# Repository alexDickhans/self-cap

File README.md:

# Self-Cap

A small self-capacitance board from the HIRO Group. An ESP32-C6-MINI-1 reads seven electrode holes along one edge. Power comes from USB-C or a single-cell battery on a JST PH connector.

Open `self-cap.kicad_pro` in KiCad 9. The electrode-hole footprint lives in `self-cap-conn.pretty`. The silkscreen reads **HIRO Group Self-Cap PCB v1**.

## Board

Top. The ESP32-C6-MINI-1 lands on the right, and the USB-C receptacle is the pair of slots on the left. The module can and the connector shell are not drawn here; the footprints are.

Bottom. J2 is the battery connector and R2 (1 kΩ) is fitted. R3–R9 are left empty.

The board is 45.2 mm × 19.8 mm, four layers, 1.6 mm. The two inner layers are ground. Eight plated holes, 2.2 mm drill on a 5.6 mm pitch, run along the long edge. GND is the hole at the module end. Hole 7 is the hole at the USB end.

| Silkscreen | ESP32-C6 pin |
| --- | --- |
| GND | GND |
| 1 | IO23 |
| 2 | IO22 |
| 3 | IO1 |
| 4 | IO5 |
| 5 | IO4 |
| 6 | IO3 |
| 7 | IO2 |

Each numbered hole is already tied to that GPIO. R3–R9 are optional 0402 resistors on the bottom, one per hole, from the electrode to a common node. That node is driven by IO19 through R2 (1 kΩ). The value on the schematic is 1 MΩ–100 MΩ; fit whatever value you want in that range, or leave them off.

D1 is the power LED. It lights when the 3.3 V rail is up. D2 is the status LED on IO15, active high, through 330 Ω.

JP1 and JP2 are open solder jumpers. Bridge JP1 to hold EN low. Bridge JP2 to hold IO9 (BOOT) low for the serial download mode. R1 is a 100 kΩ pull-up on EN.

## Power

USB-C or the battery can run the board. U3 (SPX3819) makes 3.3 V from that input. J2 pin 1 is battery positive and pin 2 is ground. Use a single lithium cell.

U2 (MAX40200) is an ideal diode from the battery onto the 5 V rail, so USB voltage stays off the cell. There is no charger on this board.

The USB 2.0 pair and the 5.1 kΩ CC pulldown are wired on one side of the receptacle (A6, A7, and A5). If a cable does nothing, flip the plug.

## Having the board made

The files in `production/` match this revision of the board. Upload those, not an older export.

### Bare boards

1. Upload [`production/self-cap-gerbers.zip`](production/self-cap-gerbers.zip). It contains the four copper layers, solder mask, silkscreen, paste, the board outline, and one Excellon drill file.
2. Check that the preview shows a 4-layer board about 45.2 mm × 19.8 mm, with eight large round holes and two slots at the USB end.
3. Order it with these settings. They match the stackup in the KiCad file and a normal prototype fab (JLCPCB, PCBWay, and the usual Gerber upload forms).

| Setting | Value |
| --- | --- |
| Layers | 4 |
| Thickness | 1.6 mm |
| Material | FR-4 |
| Outer copper | 1 oz |
| Inner copper | 0.5 oz |
| Min trace / space | 0.15 mm / 0.2 mm |
| Smallest drill | 0.3 mm vias. Electrode holes are 2.2 mm. |
| Holes | All plated, including the electrode holes. The USB shell uses plated slots. |
| Surface finish | ENIG when the fab is soldering the USB-C connector and the module. HASL is fine if you are hand-soldering. |
| Soldermask / silk | Green soldermask and white silk match the pictures. Any color works. |
| Impedance control | Leave it off. The inner layers are a ground plane. |

The USB shell copper is 0.18 mm from the outline. If the quote warns about copper-to-edge clearance, accept it only when the shell pads are still complete in the preview.

### Assembled boards

Assembly is two-sided, but the bottom only needs J2 and R2. You can order top-side assembly and solder those two yourself.

1. Upload [`production/bom.csv`](production/bom.csv) and [`production/positions.csv`](production/positions.csv) with the gerber zip.
2. The BOM comments are the values. The LCSC column is the part number stored on the schematic. Open each LCSC page and confirm the value before you pay.
3. Parts left off the board on purpose, and omitted from both files: R3–R9, JP1, JP2, and J1. J1 is the hole pattern, not a connector.
4. On the placement preview, confirm every part sits on its pads. Check the module, the USB-C connector, both LEDs, and the two SOT-23-5 parts (U2, U3). Check J2 and R2 on the bottom. Fix any rotation in the preview before paying. The position file uses KiCad’s coordinates and rotation, and the Y values are negative, which is what KiCad writes and what JLCPCB’s KiCad import expects.

R10 (5.1 kΩ), R12, and R13 (330 Ω) use 0402 and 0603 lands. Order the resistor listed in the BOM.

## Design files

| File | What it is |
| --- | --- |
| `self-cap.kicad_pro` | KiCad 9 project |
| `self-cap.kicad_sch` | Schematic |
| `self-cap.kicad_pcb` | Board |
| `self-cap-conn.pretty/` | Electrode-hole footprint |
| `self-cap.step` | Board model |
| `production/self-cap-gerbers.zip` | Gerbers and drill file to upload |
| `production/bom.csv` | Assembly BOM |
| `production/positions.csv` | Pick-and-place file |

If you change the board, export a new gerber zip, drill file, BOM, and position file from that revision before ordering.

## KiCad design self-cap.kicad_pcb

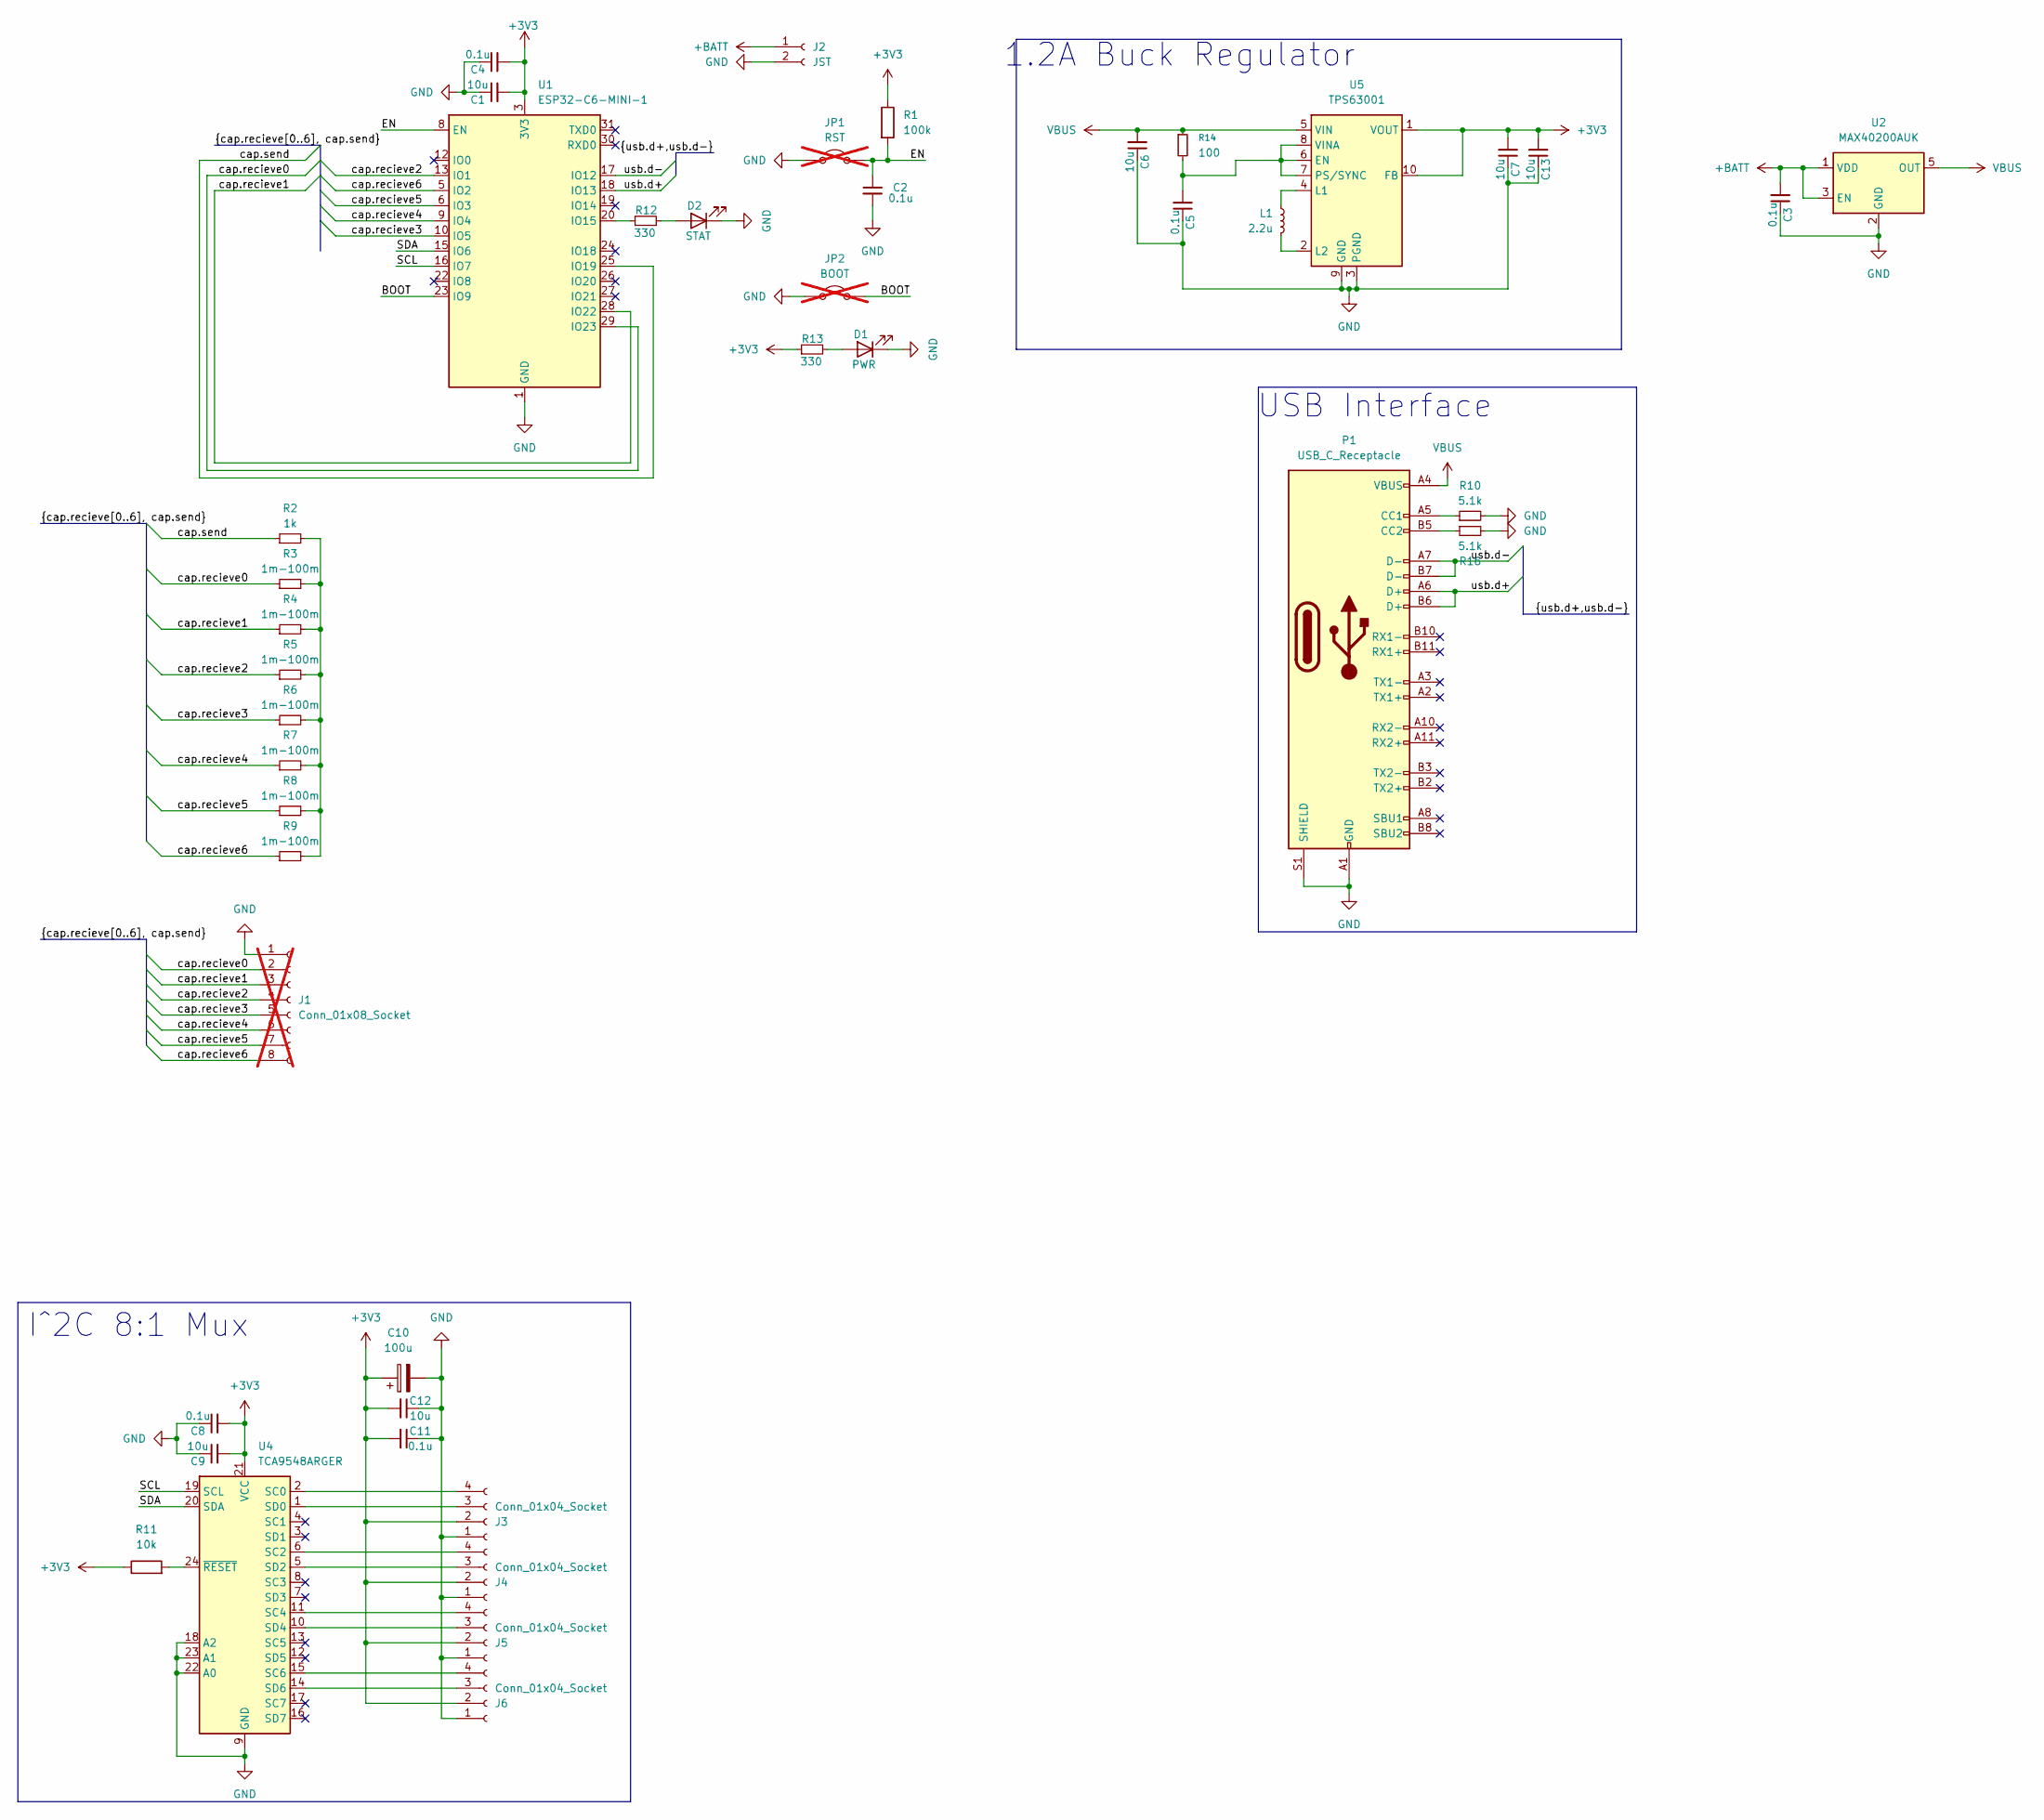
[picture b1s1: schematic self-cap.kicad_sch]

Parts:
C1, C6, C7, C9, C12, C13: 10u; C_0402_1005Metric; LCSC Part # C15525
C2, C3, C4, C5, C8, C11: 0.1u; C_0402_1005Metric; LCSC Part # C1525
C10: 100u; CP_Elec_6.3x7.7; LCSC Part # C3338
D1: PWR; LED_0603_1608Metric; LCSC Part # C2286
D2: STAT; LED_0603_1608Metric; LCSC Part # C2286
J1: Conn_01x08_Socket; self-cap-connn; not fitted
J2: JST; JST_PH_S2B-PH-SM4-TB_1x02-1MP_P2.00mm_Horizontal; LCSC Part # C295747
J3, J4, J5, J6: Conn_01x04_Socket; JST_SH_BM04B-SRSS-TB_1x04-1MP_P1.00mm_Vertical; LCSC Part # C160390
JP1: RST; SolderJumper-2_P1.3mm_Open_RoundedPad1.0x1.5mm; not fitted
JP2: BOOT; SolderJumper-2_P1.3mm_Open_RoundedPad1.0x1.5mm; not fitted
L1: 2.2u; L_Coilcraft_LPS3010; LCSC Part # C2844756
P1: USB_C_Receptacle; USB_C_Receptacle_Molex_105450-0101
R1: 100k; R_0402_1005Metric; LCSC Part # C25741
R2: 1k; R_0402_1005Metric; LCSC Part # C11702
R3, R4, R5, R6, R7, R8, R9: 1m-100m; C_0402_1005Metric; LCSC Part # C131554
R10, R16: 5.1k; C_0402_1005Metric; LCSC Part # C25905
R11: 10k; R_0402_1005Metric; LCSC Part # C25744
R12, R13: 330; C_0603_1608Metric; LCSC Part # C23138
R14: 100; R_0402_1005Metric; LCSC Part # C25076
U1: ESP32-C6-MINI-1; LCSC Part # C5736265
U2: MAX40200AUK; SOT-23-5; LCSC Part # C47118006
U4: TCA9548ARGER; Texas_RGE0024C_VQFN-24-1EP_4x4mm_P0.5mm_EP2.1x2.1mm; LCSC Part # C555456
U5: TPS63001; Texas_DRC0010J_ThermalVias; LCSC Part # C28060

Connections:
+3V3: C1.2, C4.2, C7.2, C8.2, C9.2, C10.1, C11.2, C12.2, C13.2, J3.2, J4.2, J5.2, J6.2, R1.1, R11.1, R13.1, U1.3 (3V3), U4.21 (VCC), U5.1 (VOUT), U5.10 (FB)
+BATT: C3.2, J2.1, U2.1 (VDD), U2.3 (EN)
/BOOT: JP2.2 (B), U1.23 (IO9)
/EN: C2.1, JP1.2 (B), R1.2, U1.8 (EN)
/SCL: U1.16 (IO7), U4.19 (SCL)
/SDA: U1.15 (IO6), U4.20 (SDA)
/cap.recieve0: J1.2, R3.1, U1.29 (IO23)
/cap.recieve1: J1.3, R4.1, U1.28 (IO22)
/cap.recieve2: J1.4, R5.1, U1.13 (IO1)
/cap.recieve3: J1.5, R6.1, U1.10 (IO5)
/cap.recieve4: J1.6, R7.1, U1.9 (IO4)
/cap.recieve5: J1.7, R8.1, U1.6 (IO3)
/cap.recieve6: J1.8, R9.1, U1.5 (IO2)
/cap.send: R2.1, U1.25 (IO19)
/usb.d+: P1.A6 (D+), P1.B6 (D+), U1.18 (IO13)
/usb.d-: P1.A7 (D-), P1.B7 (D-), U1.17 (IO12)
GND: C1.1, C2.2, C3.1, C4.1, C5.1, C6.1, C7.1, C8.1, C9.1, C10.2, C11.1, C12.1, C13.1, D1.1 (K), D2.1 (K), J1.1, J2.2, J3.1, J4.1, J5.1, J6.1, JP1.1 (A), JP2.1 (A), P1.A1 (GND), P1.A12 (GND), P1.B1 (GND), P1.B12 (GND), P1.S1 (SHIELD), R10.2, R16.2, U1.1 (GND), U1.2 (GND), U1.11 (GND), U1.14 (GND), U1.36 (GND), U1.37 (GND), U1.38 (GND), U1.39 (GND), U1.40 (GND), U1.41 (GND), U1.42 (GND), U1.43 (GND), U1.44 (GND), U1.45 (GND), U1.46 (GND), U1.47 (GND), U1.48 (GND), U1.49 (GND), U1.50 (GND), U1.51 (GND), U1.52 (GND), U1.53 (GND), U2.2 (GND), U4.9 (GND), U4.18 (A2), U4.22 (A0), U4.23 (A1), U5.3 (PGND), U5.9 (GND), U5.11 (PGND)
unnamed: D1.2 (A), R13.2
unnamed: D2.2 (A), R12.2
unnamed: J3.3, U4.1 (SD0)
unnamed: J3.4, U4.2 (SC0)
unnamed: J4.3, U4.5 (SD2)
unnamed: J4.4, U4.6 (SC2)
unnamed: J5.3, U4.10 (SD4)
unnamed: J5.4, U4.11 (SC4)
unnamed: J6.3, U4.14 (SD6)
unnamed: J6.4, U4.15 (SC6)
unnamed: P1.A5 (CC1), R10.1
unnamed: P1.B5 (CC2), R16.1
unnamed: R2.2, R3.2, R4.2, R5.2, R6.2, R7.2, R8.2, R9.2
unnamed: R12.1, U1.20 (IO15)
unnamed: R11.2, U4.24 (~RESET)
unnamed: C5.2, R14.2, U5.6 (EN), U5.7 (PS/SYNC), U5.8 (VINA)
unnamed: L1.1, U5.4 (L1)
unnamed: L1.2, U5.2 (L2)
VBUS: C6.2, P1.A4 (VBUS), P1.A9 (VBUS), P1.B4 (VBUS), P1.B9 (VBUS), R14.1, U2.5 (OUT), U5.5 (VIN)

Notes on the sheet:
USB Interface
1.2A Buck Regulator
I^2C 8:1 Mux

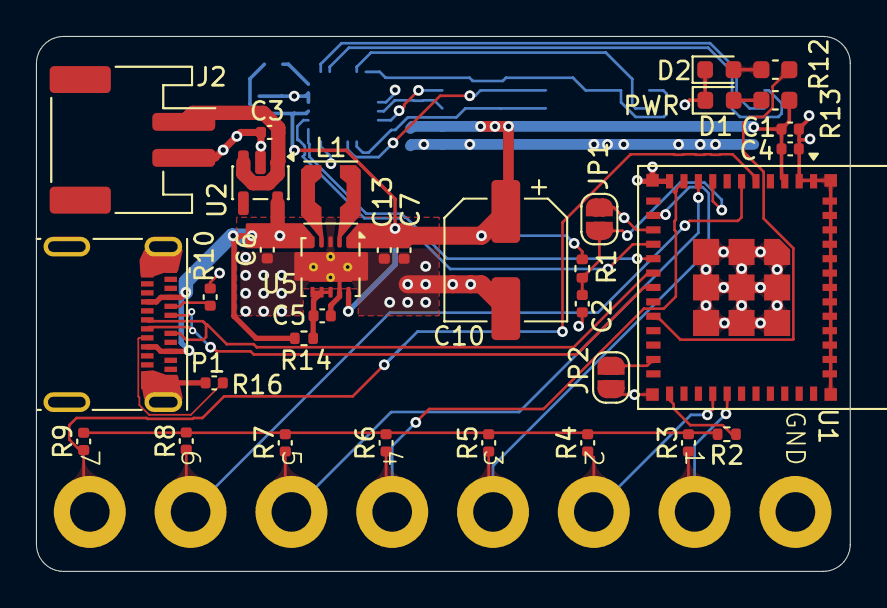
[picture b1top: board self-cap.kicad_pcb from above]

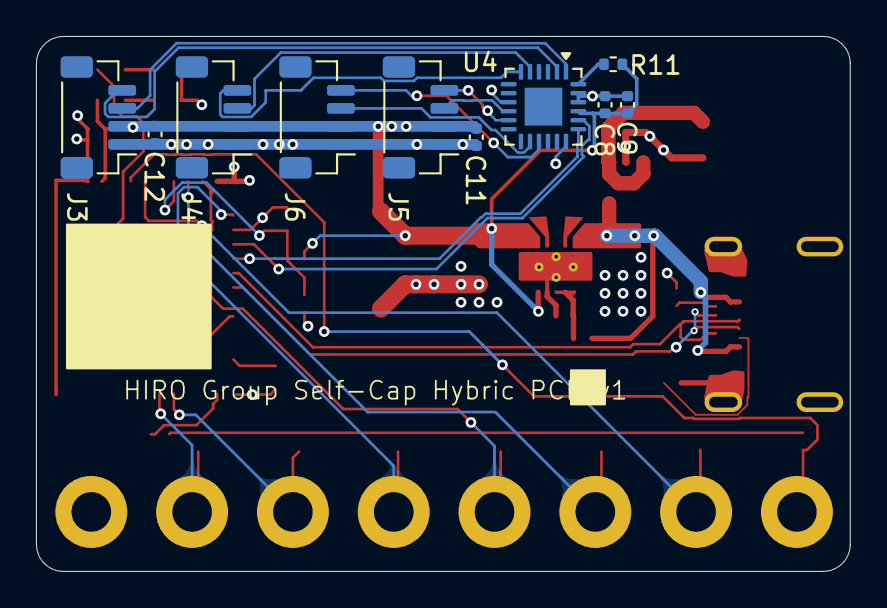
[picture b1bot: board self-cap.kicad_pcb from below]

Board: 4 copper layers, 45.2 x 29.7 mm, 44 parts (10 on the bottom side), 36 nets.

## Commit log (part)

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2025-11-17 Switching directions
2026-02-05 V3 revisions
2026-02-06 Remove lock files
2026-02-10 schematic and layout ready for manufacturing
